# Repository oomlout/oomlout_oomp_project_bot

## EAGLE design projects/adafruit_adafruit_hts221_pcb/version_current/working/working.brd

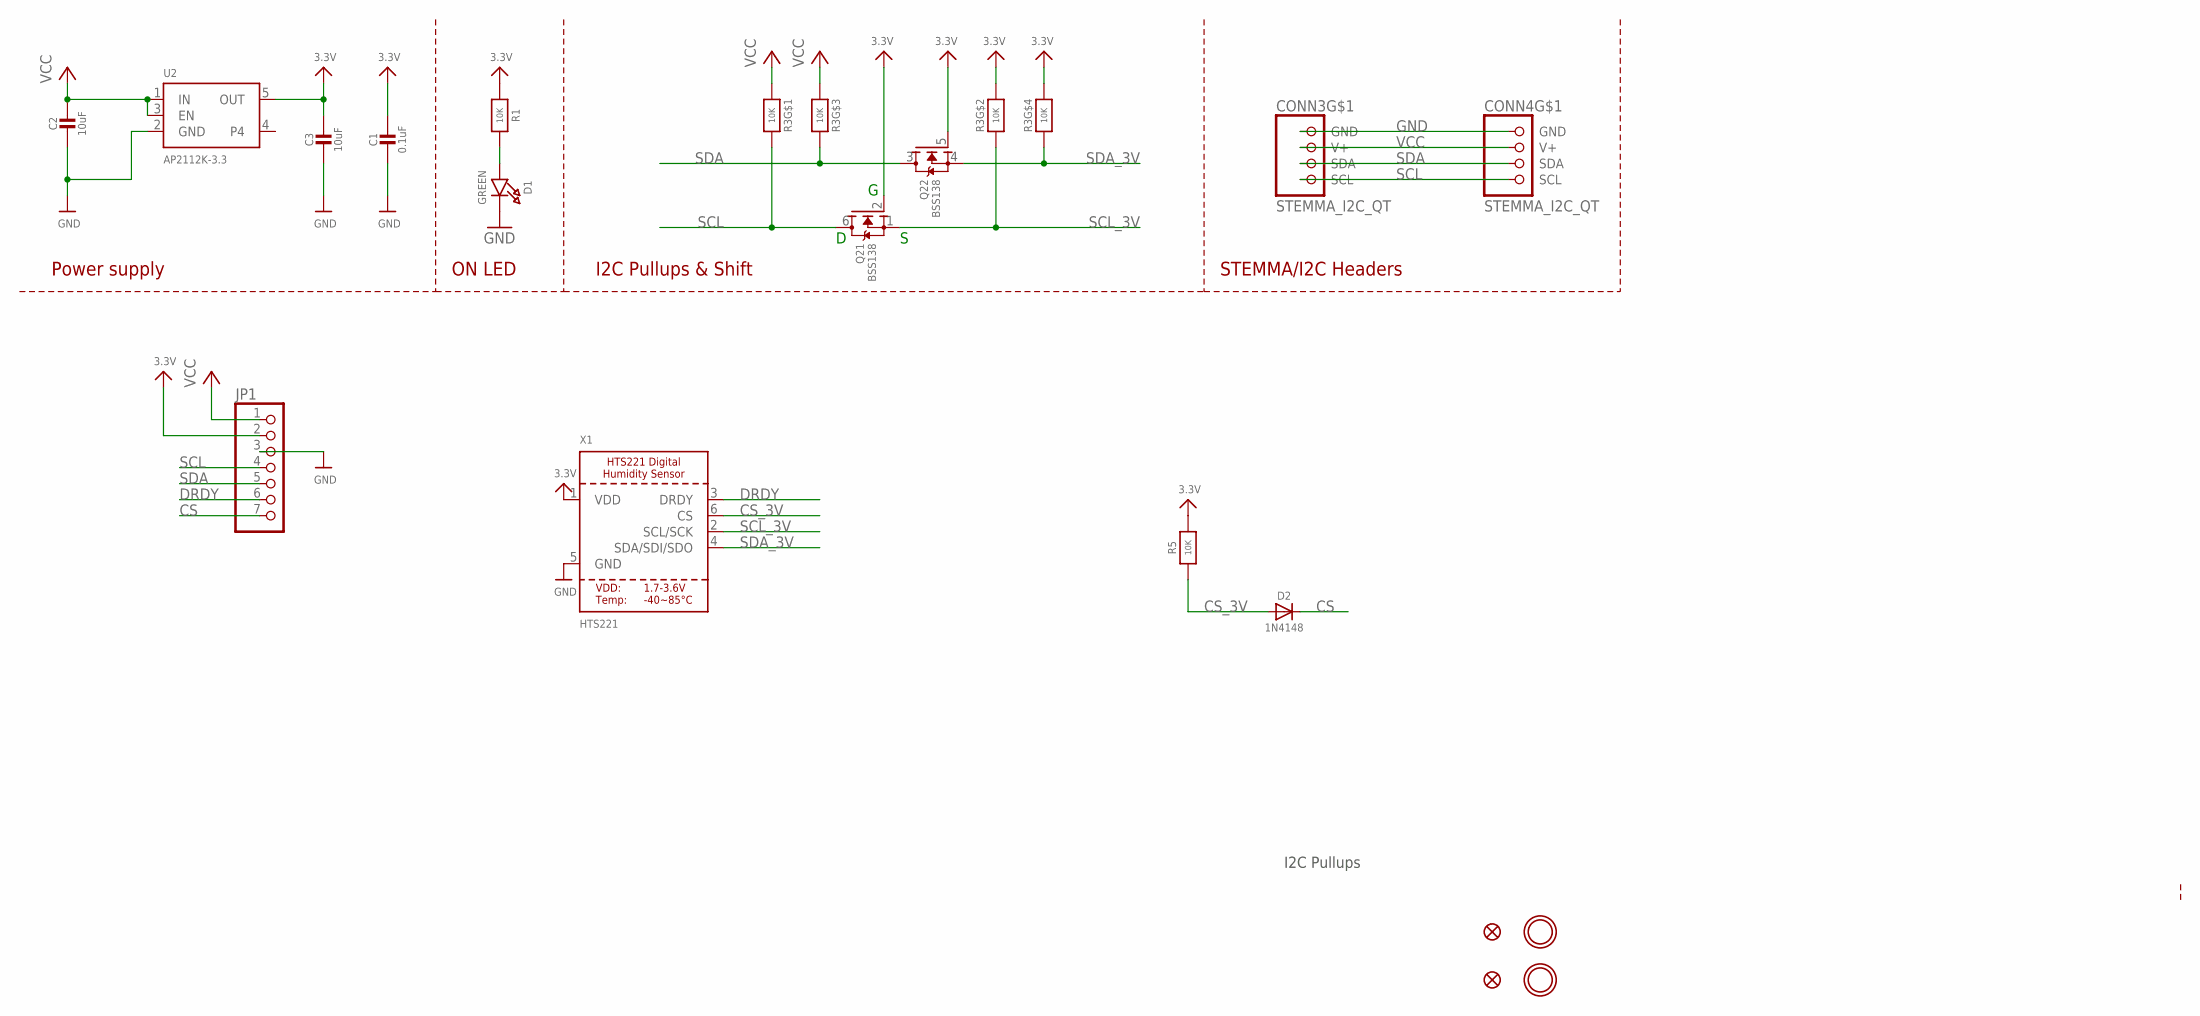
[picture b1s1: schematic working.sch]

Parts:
C1: 0.1uF; 0603-NO
C2, C3: 10uF; 0805-NO
CONN3, CONN4: STEMMA_I2C_QT; JST_SH4
D1: GREEN; CHIPLED_0603_NOOUTLINE
D2: 1N4148; SOD-323
FID3, FID4: FIDUCIAL_1MM
JP1: HEADER-1X770MIL; 1X07_ROUND_70
Q2: BSS138; SOT363
R1, R5: 10K; 0603-NO
R3: 10K; RESPACK_4X0603
U2: AP2112K-3.3; SOT23-5
U$1, U$17: MOUNTINGHOLE2.5; MOUNTINGHOLE_2.5_PLATED
X1: HTS221; HLGA-6L

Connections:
3.3V: C1.1, C3.1, JP1.2, Q2.2 (G), Q2.5 (G), R1.1, R3.2 (1), R3.4 (1), R5.2, U2.5 (OUT), X1.1 (VDD)
CS: D2.C, JP1.7
CS_3V: D2.A, R5.1, X1.6 (CS)
DRDY: JP1.6, X1.3 (DRDY)
GND: C1.2, C2.2, C3.2, CONN3.1 (GND), CONN4.1 (GND), D1.C, JP1.3, U2.2 (GND), X1.5 (GND)
unnamed: D1.A, R1.2
SCL: CONN3.4 (SCL), CONN4.4 (SCL), JP1.4, Q2.6 (D), R3.8 (2)
SCL_3V: Q2.1 (S), R3.7 (2), X1.2 (SCL/SCK)
SDA: CONN3.3 (SDA), CONN4.3 (SDA), JP1.5, Q2.3 (D), R3.6 (2)
SDA_3V: Q2.4 (S), R3.5 (2), X1.4 (SDA/SDI/SDO)
VCC: C2.1, CONN3.2 (V+), CONN4.2 (V+), JP1.1, R3.1, R3.3 (1), U2.1 (IN), U2.3 (EN)

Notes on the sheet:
I2C Pullups & Shift
STEMMA/I2C Headers
ON LED
Power supply
I2C Pullups

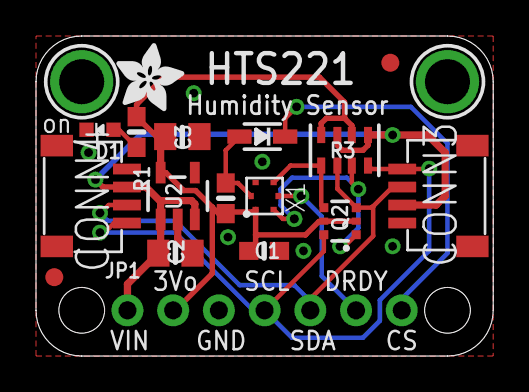
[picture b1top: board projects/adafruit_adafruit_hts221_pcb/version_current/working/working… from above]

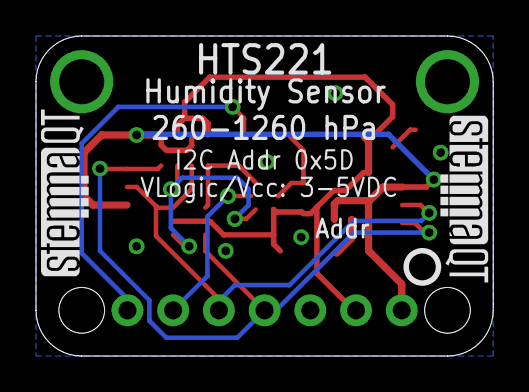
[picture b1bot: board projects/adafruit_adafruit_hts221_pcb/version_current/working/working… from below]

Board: 2 copper layers, 25.4 x 17.8 mm, 22 parts (3 on the bottom side), 11 nets.

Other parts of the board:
U$4: ADAFRUIT_3.5MM
U$25: PCBFEAT-REV-040
U$30, U$31: STEMMAQT

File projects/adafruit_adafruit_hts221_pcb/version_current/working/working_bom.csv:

Row,Description,Part,References,Value,Footprint,Quantity Per PCB,Status,Datasheet
1,,CAP_CERAMIC0603_NO,C1,0.1uF,0603-NO,1, ,
2,,CAP_CERAMIC0805-NOOUTLINE,C2 C3,10uF,0805-NO,2, ,
3,,STEMMA_I2C_QT,CONN3 CONN4,STEMMA_I2C_QT,JST_SH4,2, ,
4,,DIODESOD-323,D2,1N4148,SOD-323,1, ,
5,,LED0603_NOOUTLINE,D1,GREEN,CHIPLED_0603_NOOUTLINE,1, ,
6,,HEADER-1X770MIL,JP1,HEADER-1X770MIL,1X07_ROUND_70,1, ,
7,,MOSFET-N_DUAL,Q2,BSS138,SOT363,1, ,
8,,RESISTOR_0603_NOOUT,R1 R5,10K,0603-NO,2, ,
9,,RESISTOR_4PACK,R3,10K,RESPACK_4X0603,1, ,
10,,VREG_SOT23-5,U2,AP2112K-3.3,SOT23-5,1, ,
11,,HTS221,X1,HTS221,HLGA-6L,1, ,





Project info:
Schematic:,working
Variant:,default
Revision:,
Date:,2023-08-03_17-21-22
KiCad Version:,7.0.6-7.0.6~ubuntu22.04.1
Statistics:
Component Groups:,11
Component Count:,14 (0 SMD/ 0 THT)
Fitted Components:,14 (0 SMD/ 0 THT)
Number of PCBs:,1
Total Components:,14

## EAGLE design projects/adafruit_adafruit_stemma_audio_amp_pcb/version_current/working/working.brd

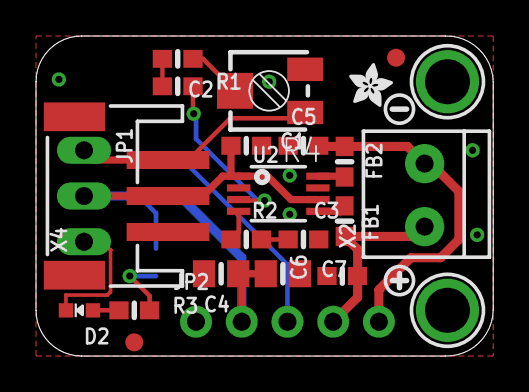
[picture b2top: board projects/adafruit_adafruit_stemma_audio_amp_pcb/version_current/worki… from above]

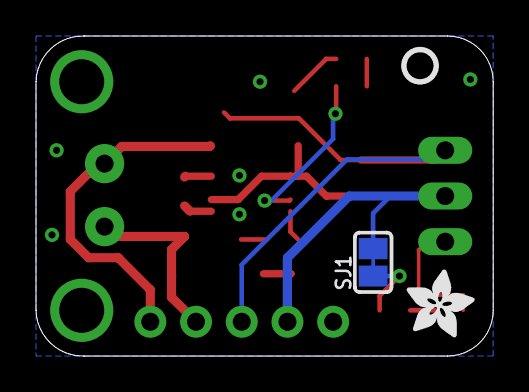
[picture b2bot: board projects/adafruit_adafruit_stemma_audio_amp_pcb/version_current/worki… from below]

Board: 2 copper layers, 25.4 x 17.8 mm, 42 parts (13 on the bottom side), 14 nets.

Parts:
C1, C2, C3: 0.1uF; 0603-NO
C4, C7: 10uF; 0805-NO
C5, C6: 220pF; 0603-NO
D2: GREEN; CHIPLED_0603_NOOUTLINE
FB1, FB2: Ferrite; 0603-NO
FID2, FID3: FIDUCIAL_1MM
JP1: 0.1" Header; 1X03_OVAL
JP2: 1X05_ROUND_70
PLABEL0: PLABEL0
PLABEL1: PLABEL1
PLABEL2: PLABEL2
PLABEL3: PLABEL3
PLABEL4: PLABEL4
PLABEL5: PLABEL5
PLABEL6: PLABEL6
PLABEL7: PLABEL7
PLABEL8: PLABEL8
PLABEL9: PLABEL9
PLABEL10: PLABEL10
PLABEL11: PLABEL11
PLABEL12: PLABEL12
R1, R2: 30K; 0603-NO
R3: 10K; 0603-NO
R4: 10K Trim; RTRIM3314J
SJ1: SOLDERJUMPER_CLOSEDWIRE
U2: PAM8302; MSOP8_0.65MM
U$1, U$8: MOUNTINGHOLE2.5; MOUNTINGHOLE_2.5_PLATED
U$3: SYMBOL_PLUS
U$5: PCBFEAT-REV-040
U$9: SYMBOL_MINUS
U$12: ADAFRUIT_3.5MM
U$19: ADAFRUIT_2.5MM
X2: 3.5mm; TERMBLOCK_1X2-3.5MM
X4: JST PH 3; JSTPH3

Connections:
GND: C1.2, C3.2, C4.2, C5.2, C6.2, C7.2, D2.C, JP1.3, JP2.1, R4.1, U2.7, X4.1
IN+: R1.2, U2.3
IN-: R2.2, U2.4
unnamed: R3.2, SJ1.1
unnamed: C3.1, R2.1
unnamed: C2.1, R1.1
unnamed: C2.2, R4.2
unnamed: D2.A, R3.1
OUT+: FB1.1, U2.5
OUT-: FB2.1, U2.8
SIGNAL: JP1.1, JP2.3, R4.3, X4.3
VIN: C1.1, C4.1, C7.1, JP1.2, JP2.2, SJ1.2, U2.1, U2.6, X4.2
VO+: C6.1, FB1.2, JP2.4, X2.2
VO-: C5.1, FB2.2, JP2.5, X2.1

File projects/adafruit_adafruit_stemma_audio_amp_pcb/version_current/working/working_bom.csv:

Row,Description,Part,References,Value,Footprint,Quantity Per PCB,Status,Datasheet
1,,CAP_CERAMIC0603_NO,C5 C6,220pF,0603-NO,2, ,
2,,CAP_CERAMIC0603_NO,C1 C2 C3,0.1uF,0603-NO,3, ,
3,,CAP_CERAMIC0805-NOOUTLINE,C4 C7,10uF,0805-NO,2, ,
4,,LED0603_NOOUTLINE,D2,GREEN,CHIPLED_0603_NOOUTLINE,1, ,
5,,FERRITE-0603NO,FB1 FB2,Ferrite,0603-NO,2, ,
6,,HEADER-1X3,JP1,"0.1"" Header",1X03_OVAL,1, ,
7,,HEADER-1X570MIL,JP2,HEADER-1X570MIL,1X05_ROUND_70,1, ,
8,,RESISTOR_0603_NOOUT,R3,10K,0603-NO,1, ,
9,,R-TRIMM3314J,R4,10K Trim,RTRIM3314J,1, ,
10,,RESISTOR_0603_NOOUT,R1 R2,30K,0603-NO,2, ,
11,,AUDIOAMP_PAM8302A,U2,PAM8302,MSOP8_0.65MM,1, ,
12,,TERMBLOCK_1X2_3.5MM,X2,3.5mm,TERMBLOCK_1X2-3.5MM,1, ,
13,,CON_JST_PH_3PIN,X4,JST PH 3,JSTPH3,1, ,





Project info:
Schematic:,working
Variant:,default
Revision:,
Date:,2023-08-03_17-21-23
KiCad Version:,7.0.6-7.0.6~ubuntu22.04.1
Statistics:
Component Groups:,13
Component Count:,19 (0 SMD/ 0 THT)
Fitted Components:,19 (0 SMD/ 0 THT)
Number of PCBs:,1
Total Components:,19

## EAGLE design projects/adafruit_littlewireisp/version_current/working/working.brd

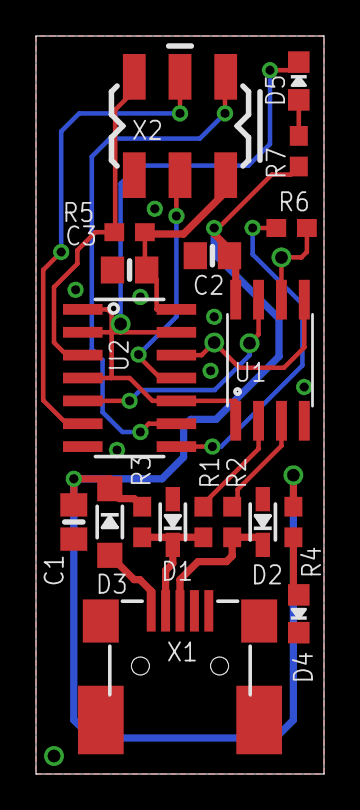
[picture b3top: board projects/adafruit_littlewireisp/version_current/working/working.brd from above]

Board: 2 copper layers, 16.0 x 41.0 mm, 19 parts (0 on the bottom side), 19 nets.

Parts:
C1: 4u7; 0805-NO
C2, C3: 100n; 0805-NO
D1, D2: 3V6; SOD-323
D3: SOD-123
D4, D5: CHIPLED_0805_NOOUTLINE
R1, R2: 68R; 0603-NO
R3: 1K5; 0603-NO
R4, R6: 470R; 0603-NO
R5: 10K; 0603-NO
R7: 1K; 0603-NO
U1: ATTINY45; SO08-EIAJ
U2: 74AHC125-SOIC14; SOIC14
X1: USB-MINIB_LARGER
X2: AVR ISP; 2X3_SMD

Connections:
5.0V: C1.1, C2.2, D3.C, R3.2, R4.1, R7.1, U1.8
GND: C1.2, C2.1, C3.1, D1.A, D2.A, D4.C, U1.4, U2.7, X1.GND, X1.GND1, X1.GND2, X1.GND3, X1.GND4, X2.6
MISO-HV: R6.1, U2.8
MISO-LV: U2.9, X2.1
MOSI-HV: U1.5, U2.12
MOSI-LV: U2.11, X2.4
unnamed: D1.C, R1.1, R3.1, X1.D-
unnamed: D2.C, R2.1, X1.D+
unnamed: D5.A, R7.2
unnamed: R1.2, U1.2
unnamed: R2.2, U1.3
unnamed: D3.A, X1.VBUS
unnamed: D4.A, R4.2
PB2/MISO: R6.2, U1.6
RST-HV: D5.C, U1.1, U2.1, U2.2, U2.4, U2.10, U2.13
RST-LV: R5.1, U2.3, X2.5
SCK-HV: U1.7, U2.5
SCK-LV: U2.6, X2.3
VDDIO: C3.2, R5.2, U2.14, X2.2

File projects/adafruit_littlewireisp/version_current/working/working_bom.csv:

Row,Description,Part,References,Value,Footprint,Quantity Per PCB,Status,Datasheet
1,,CAP_CERAMIC0805-NOOUTLINE,C2 C3,100n,0805-NO,2, ,
2,,CAP_CERAMIC0805-NOOUTLINE,C1,4u7,0805-NO,1, ,
3,,DIODE-ZENERSOD323,D1 D2,3V6,SOD-323,2, ,
4,,DIODESOD-123,D3,DIODESOD-123,SOD-123,1, ,
5,,LED0805_NOOUTLINE,D4 D5,LED0805_NOOUTLINE,CHIPLED_0805_NOOUTLINE,2, ,
6,,RESISTOR_0603_NOOUT,R1 R2,68R,0603-NO,2, ,
7,,RESISTOR_0603_NOOUT,R4 R6,470R,0603-NO,2, ,
8,,RESISTOR_0603_NOOUT,R7,1K,0603-NO,1, ,
9,,RESISTOR_0603_NOOUT,R3,1K5,0603-NO,1, ,
10,,RESISTOR_0603_NOOUT,R5,10K,0603-NO,1, ,
11,,74125-SOIC14,U2,74125-SOIC14,SOIC14,1, ,
12,,ATTINY45,U1,ATTINY45,SO08-EIAJ,1, ,
13,,AVR_SPI_PRG_6SMD,X2,AVR_SPI_PRG_6SMD,2X3_SMD,1, ,
14,,USBMINIBLARGE,X1,USBMINIBLARGE,USB-MINIB_LARGER,1, ,





Project info:
Schematic:,working
Variant:,default
Revision:,
Date:,2023-08-03_17-21-23
KiCad Version:,7.0.6-7.0.6~ubuntu22.04.1
Statistics:
Component Groups:,14
Component Count:,19 (0 SMD/ 0 THT)
Fitted Components:,19 (0 SMD/ 0 THT)
Number of PCBs:,1
Total Components:,19

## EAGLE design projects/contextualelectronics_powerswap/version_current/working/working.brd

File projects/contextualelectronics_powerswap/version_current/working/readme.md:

# PowerSwap by ContextualElectronics  
This is a harvested standardized copy of a project from github.  
The original project can be found at:  
https://github.com/ContextualElectronics/PowerSwap  
Please consult that link for additional, details, files, and license information.  
Note: It was auto harvested and if the original repo had more than one board file or anything out of the ordinary the files here are likely not representative.

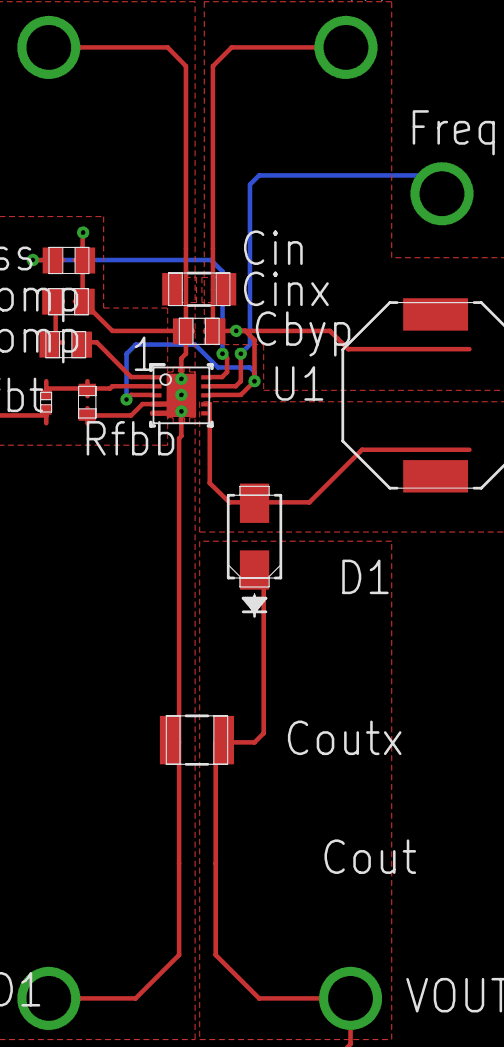
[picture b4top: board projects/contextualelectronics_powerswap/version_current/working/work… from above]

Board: 4 copper layers, 16 parts (0 on the bottom side), 9 nets.

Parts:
Cbyp: 0805
Ccomp: 0805
Cin: 1206
Cout: 1210
Css: 0805
D1: SMA
Freq: TP-1502
GND, GND1: TP-1502
L1: SRU1048
Rcomp: 0805
Rfbb: 0603
Rfbt: 0402
U1: DRC0010A
VIN: TP-1502
VOUT: TP-1502

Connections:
0: Cbyp.2, Ccomp.2, Cin.2, Cout.2, Css.2, GND.1, GND1.1, Rfbb.2, U1.4, U1.5, U1.11
1: Cbyp.1, Cin.1, L1.1, U1.3, U1.8, VIN.1
2: Cout.1, D1.1, Rfbt.1, VOUT.1
4: D1.2, L1.2, U1.6, U1.7
5: Rcomp.1, U1.1
6: Rfbb.1, Rfbt.2, U1.2
7: Ccomp.1, Rcomp.2
13: Freq.1, U1.9
14: Css.1, U1.10

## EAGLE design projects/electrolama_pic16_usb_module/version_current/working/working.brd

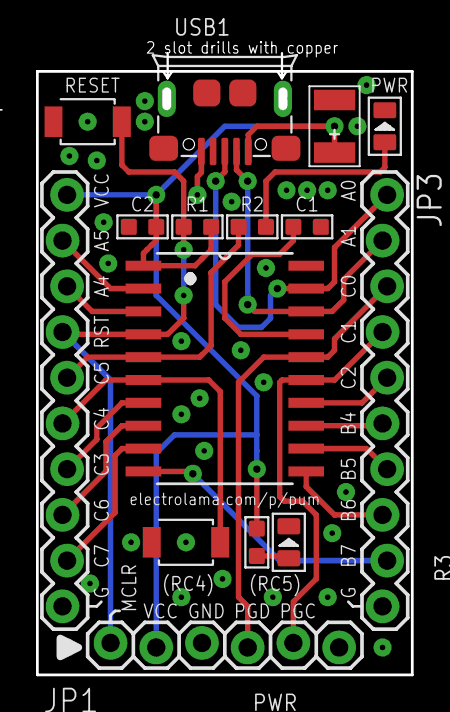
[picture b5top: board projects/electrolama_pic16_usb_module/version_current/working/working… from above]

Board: 2 copper layers, 20.8 x 34.5 mm, 15 parts (0 on the bottom side), 22 nets.

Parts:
C1: 1uf; C0603
C2: 100nf; C0603
C3: 22uf; AVX-B
D1: GREEN-0805; LED-0805
D2: YELLOW-0805; LED-0805
JP1: 1X06_LOCK
JP2, JP3: M10LOCK; 1X10_LOCK
R1: 10K; R0603
R2, R3: 200R 1/10W; R0603
SW1, SW2: B3U-1000P-2P-SMD; SW2-2.6-3.0X2.5X1.2+0.4MM
U1: PIC16F1459-I/SO; SOIC127P1030X265-20N
USB1: ST-USB-001G; MICRO-USB5+4P-SMD-0.65-B

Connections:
GND: C1.1, C2.1, C3.-, D1.-, D2.-, JP1.3, JP2.10, JP3.10, SW1.2, SW2.2, U1.20, USB1.5
MCLR: JP1.1, JP2.4, R1.1, SW1.1, U1.4
unnamed: D2.+, R2.2
unnamed: D1.+, R3.2
RA0/DP: JP3.1, U1.19, USB1.3
RA1/DM: JP3.2, U1.18, USB1.2
RA4: JP2.3, U1.3
RA5: JP2.2, U1.2
RB4: JP3.6, U1.13
RB5: JP3.7, U1.12
RB6: JP3.8, U1.11
RB7: JP3.9, U1.10
RC0/PGD: JP1.4, JP3.3, U1.16
RC1/PGC: JP1.5, JP3.4, U1.15
RC2: JP3.5, U1.14
RC3: JP2.7, U1.7
RC4: JP2.6, SW2.1, U1.6
RC5: JP2.5, R2.1, U1.5
RC6: JP2.8, U1.8
RC7: JP2.9, U1.9
VCC: C2.2, C3.+, JP1.2, JP2.1, R1.2, R3.1, U1.1, USB1.1
VUSB: C1.2, U1.17

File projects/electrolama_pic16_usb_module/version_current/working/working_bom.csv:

"Id";"Designator";"Footprint";"Quantity";"Designation";"Supplier and ref";
1;"JP1";"1X06_LOCK";1;"";;;
2;"USB1";"MICRO-USB5+4P-SMD-0.65-B";1;"ST-USB-001G";;;
3;"C2";"C0603";1;"100nf";;;
4;"SW1,SW2";"SW2-2.6-3.0X2.5X1.2+0.4MM";2;"B3U-1000P-2P-SMD";;;
5;"D2";"LED-0805";1;"YELLOW-0805";;;
6;"C3";"AVX-B";1;"22uf";;;
7;"JP3,JP2";"1X10_LOCK";2;"M10LOCK";;;
8;"U1";"SOIC127P1030X265-20N";1;"PIC16F1459-I/SO";;;
9;"R2,R3";"R0603";2;"200R 1/10W";;;
10;"D1";"LED-0805";1;"GREEN-0805";;;
11;"C1";"C0603";1;"1uf";;;
12;"R1";"R0603";1;"10K";;;

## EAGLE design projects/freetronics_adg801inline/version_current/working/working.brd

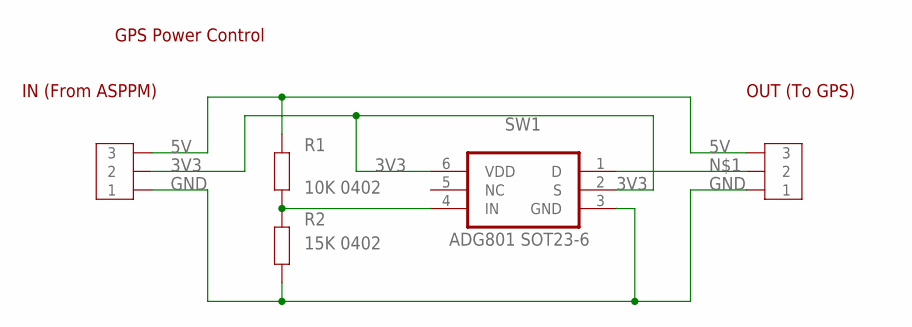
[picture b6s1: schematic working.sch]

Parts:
JP1, JP2: 3PIN_SMD; 1X3-2MM
R1: 10K 0402; 0402
R2: 15K 0402; 0402
SW1: ADG801 SOT23-6; SOT23-6

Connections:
3V3: JP1.P$2 (2), SW1.2 (S), SW1.6 (VDD)
5V: JP1.P$3 (3), JP2.P$3 (3), R1.2
GND: JP1.P$1 (1), JP2.P$1 (1), R2.1, SW1.3 (GND)
unnamed: JP2.P$2 (2), SW1.1 (D)
unnamed: R1.1, R2.2, SW1.4 (IN)

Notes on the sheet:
GPS Power Control
IN (From ASPPM)
OUT (To GPS)

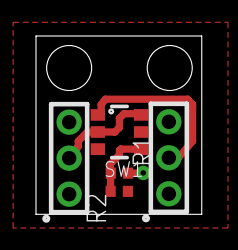
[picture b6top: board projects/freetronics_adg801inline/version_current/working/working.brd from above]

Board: 4 copper layers, 9.2 x 9.9 mm, 5 parts (0 on the bottom side), 5 nets.

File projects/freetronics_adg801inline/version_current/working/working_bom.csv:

"Id";"Designator";"Footprint";"Quantity";"Designation";"Supplier and ref";
1;"@HOLE0,@HOLE1";"";2;"";;;
2;"R1";"0402";1;"10K 0402";;;
3;"JP1,JP2";"1X3-2MM";2;"";;;
4;"SW1";"SOT23-6";1;"ADG801 SOT23-6";;;
5;"R2";"0402";1;"15K 0402";;;

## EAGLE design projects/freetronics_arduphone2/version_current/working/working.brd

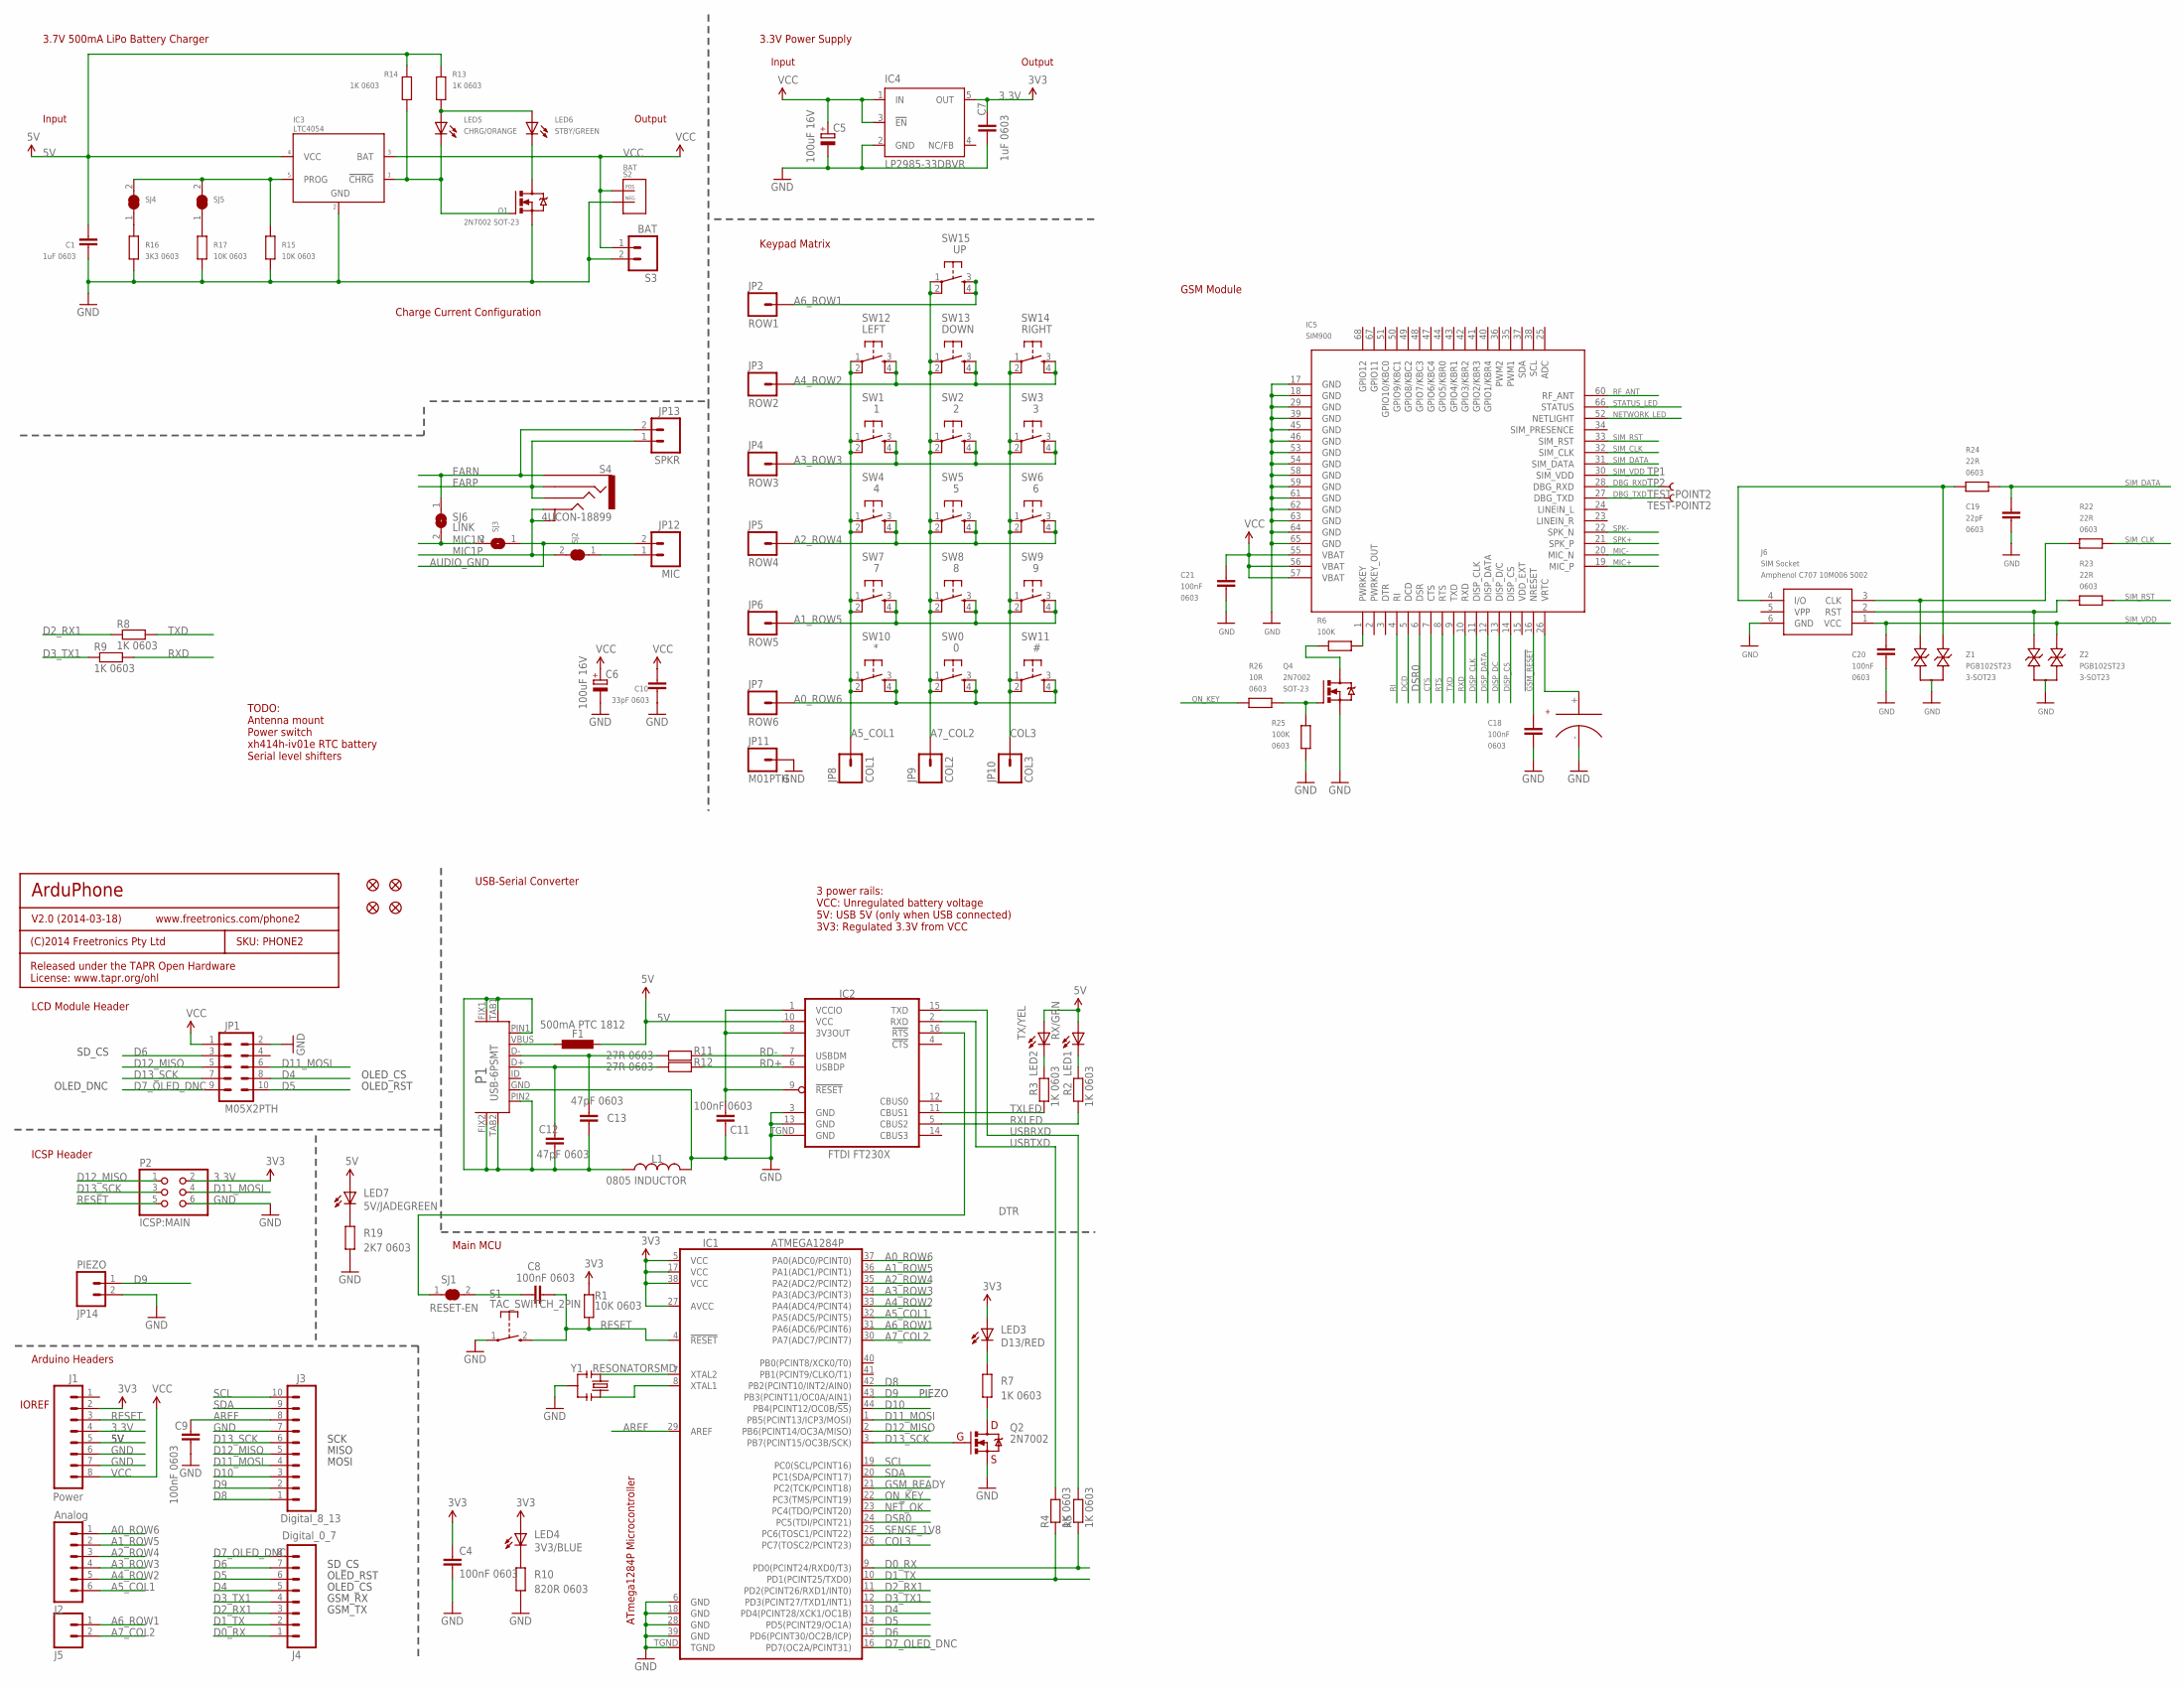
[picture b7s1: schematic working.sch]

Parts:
C1, C7: 1uF 0603; 0603
C4, C8, C9, C11: 100nF 0603; 0603
C5, C6: 100uF 16V; PANASONIC_D
C10: 33pF 0603; 0603@1
C12, C13: 47pF 0603; C0603
C18, C20, C21: 100nF; 0603
C19: 22pF; 0603
F1: 500mA PTC 1812; L1812
IC1: ATMEGA1284P; QFN-44M1
IC2: FT230X; QFN-16
IC3: LTC4054; SOT23-5
IC4: LP2985-33DBVR; TEXAS_SOT23-DBV
IC5: SIM900
J1: Power; 1X08
J2: Analog; 1X06
J3: Digital_8_13; 1X10
J4: Digital_0_7; 1X08
J5: M02PTH; 1X02
J6: SIM Socket; SIMHOLDER3
JP1: M05X2PTH; AVR_ICSP
JP2: ROW1; 1X01
JP3: ROW2; 1X01
JP4: ROW3; 1X01
JP5: ROW4; 1X01
JP6: ROW5; 1X01
JP7: ROW6; 1X01
JP8: COL1; 1X01
JP9: COL2; 1X01
JP10: COL3; 1X01
JP11: M01PTH; 1X01
JP12: MIC; 1X02
JP13: SPKR; 1X02
JP14: PIEZO; 1X02
L1: 0805 INDUCTOR; 0805-LARGE
LED1: RX/GRN; LED-0603
LED2: TX/YEL; LED-0603
LED3: D13/RED; LED-0603
LED4: 3V3/BLUE; LED-0603
LED5: CHRG/ORANGE; LED-0603
LED6: STBY/GREEN; LED-0603
LED7: 5V/JADEGREEN; LED-0603
P1: USB-6PSMT; USB-MICROB-MB05PMXX
P2: ICSP:MAIN; 2X03
Q1: 2N7002 SOT-23; SOT23-3
Q2, Q4: 2N7002; SOT23-3
R1, R15, R17: 10K 0603; 0603
R2, R3, R4, R5, R7, R8, R9, R13, R14: 1K 0603; 0603
R6, R25: 100K; 0603
R10: 820R 0603; 0603
R11, R12: 27R 0603; 0603
R16: 3K3 0603; 0603
R19: 2K7 0603; 0603
R22, R23, R24: 22R; 0603
R26: 10R; 0603
S1: TAC_SWITCH_2PIN; TACTILE_SWITCH_SMD_2PIN_TINY
S2: BAT; JST-2MM-TH-RA
S3: BAT; 1X02
S4: 4UCON-18899
SJ1: RESET-EN; SJC
SJ2, SJ4, SJ5: SJCN; SJC
SJ3: SJ
SJ6: LINK; SJ
SW0: 0; TACTILE-PTH
SW1: 1; TACTILE-PTH
SW2: 2; TACTILE-PTH
SW3: 3; TACTILE-PTH
SW4: 4; TACTILE-PTH
SW5: 5; TACTILE-PTH
SW6: 6; TACTILE-PTH
SW7: 7; TACTILE-PTH
SW8: 8; TACTILE-PTH
SW9: 9; TACTILE-PTH
SW10: *; TACTILE-PTH
SW11: #; TACTILE-PTH
SW12: LEFT; TACTILE-PTH
SW13: DOWN; TACTILE-PTH
SW14: RIGHT; TACTILE-PTH
SW15: UP; TACTILE-PTH
TP1, TP2: TEST-POINT2; PAD.02X.02
U$5, U$6, U$7, U$14: FIDUCIAL1X2.5; FIDUCIAL-1X2.5
U$9: XH414H-IV01E; 414-VA5R
Y1: RESONATORSMD; RESONATOR-SMD
Z1, Z2: PGB102ST23; SOT23-3

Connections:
3.3V: C4.1, C7.2, IC1.5 (VCC), IC1.17 (VCC), IC1.27 (AVCC), IC1.38 (VCC), IC4.5 (OUT), J1.2, J1.4, LED3.A, LED4.A, P2.2, R1.2
5V: C1.2, F1.2, IC2.10 (VCC), IC3.4 (VCC), J1.5, LED1.A, LED2.A, LED7.A, R13.1, R14.1
!GSM_RESET: C18.2, IC5.16 (NRESET)
A0_ROW6: IC1.37 (PA0(ADC0/PCINT0)), J2.1, JP7.1, SW0.3, SW0.4, SW10.3, SW10.4, SW11.3, SW11.4
A1_ROW5: IC1.36 (PA1(ADC1/PCINT1)), J2.2, JP6.1, SW7.3, SW7.4, SW8.3, SW8.4, SW9.3, SW9.4
A2_ROW4: IC1.35 (PA2(ADC2/PCINT2)), J2.3, JP5.1, SW4.3, SW4.4, SW5.3, SW5.4, SW6.3, SW6.4
A3_ROW3: IC1.34 (PA3(ADC3/PCINT3)), J2.4, JP4.1, SW1.3, SW1.4, SW2.3, SW2.4, SW3.3, SW3.4
A4_ROW2: IC1.33 (PA4(ADC4/PCINT4)), J2.5, JP3.1, SW12.3, SW12.4, SW13.3, SW13.4, SW14.3, SW14.4
A5_COL1: IC1.32 (PA5(ADC5/PCINT5)), J2.6, JP8.1, SW1.1, SW1.2, SW4.1, SW4.2, SW7.1, SW7.2, SW10.1, SW10.2, SW12.1, SW12.2
A6_ROW1: IC1.31 (PA6(ADC6/PCINT6)), J5.1, JP2.1, SW15.3, SW15.4
A7_COL2: IC1.30 (PA7(ADC7/PCINT7)), J5.2, JP9.1, SW0.1, SW0.2, SW2.1, SW2.2, SW5.1, SW5.2, SW8.1, SW8.2, SW13.1, SW13.2, SW15.1, SW15.2
AREF: C9.1, IC1.29 (AREF), J3.8
AUDIO_GND: JP12.2, SJ3.1
COL3: IC1.26 (PC7(TOSC2/PCINT23)), JP10.1, SW3.1, SW3.2, SW6.1, SW6.2, SW9.1, SW9.2, SW11.1, SW11.2, SW14.1, SW14.2
CTS: IC5.7 (CTS)
D0_RX: IC1.9 (PD0(PCINT24/RXD0/T3)), J4.1, R5.1
D1_TX: IC1.10 (PD1(PCINT25/TXD0)), J4.2, R4.1
D2_RX1: IC1.11 (PD2(PCINT26/RXD1/INT0)), J4.3, R8.1
D3_TX1: IC1.12 (PD3(PCINT27/TXD1/INT1)), J4.4, R9.1
D4: IC1.13 (PD4(PCINT28/XCK1/OC1B)), J4.5, JP1.8
D5: IC1.14 (PD5(PCINT29/OC1A)), J4.6, JP1.10
D6: IC1.15 (PD6(PCINT30/OC2B/ICP)), J4.7, JP1.3
D7_OLED_DNC: IC1.16 (PD7(OC2A/PCINT31)), J4.8, JP1.9
D8: IC1.42 (PB2(PCINT10/INT2/AIN0)), J3.1
D9: IC1.43 (PB3(PCINT11/OC0A/AIN1)), J3.2, JP14.1
D10: IC1.44 (PB4(PCINT12/OC0B/!SS!)), J3.3
D11_MOSI: IC1.1 (PB5(PCINT13/ICP3/MOSI)), J3.4, JP1.6, P2.4
D12_MISO: IC1.2 (PB6(PCINT14/OC3A/MISO)), J3.5, JP1.5, P2.1
D13_SCK: IC1.3 (PB7(PCINT15/OC3B/SCK)), J3.6, JP1.7, P2.3, Q2.1 (G)
DBG_RXD: IC5.28 (DBG_RXD), TP1.P$1
DBG_TXD: IC5.27 (DBG_TXD), TP2.P$1
DCD: IC5.5 (DCD)
DISP_CLK: IC5.11 (DISP_CLK)
DISP_CS: IC5.14 (DISP_CS)
DISP_DATA: IC5.12 (DISP_DATA)
DISP_DC: IC5.13 (DISP_D/C)
DSR0: IC1.24 (PC5(TDI/PCINT21)), IC5.6 (DSR)
DTR: IC2.16 (!RTS), SJ1.1
EARN: JP13.2, S4.1, SJ6.1
EARP: JP13.1, S4.3, S4.4
GND: C1.1, C4.2, C5.-, C6.-, C7.1, C9.2, C10.1, C11.2, C18.1, C19.1, C20.1, C21.1, IC1.6 (GND), IC1.18 (GND), IC1.28 (GND), IC1.39 (GND), IC1.TGND, IC2.3 (GND), IC2.13 (GND), IC2.TGND (GND), IC3.2 (GND), IC4.2 (GND), IC5.17 (GND), IC5.18 (GND), IC5.29 (GND), IC5.39 (GND), IC5.45 (GND), IC5.46 (GND), IC5.53 (GND), IC5.54 (GND), IC5.58 (GND), IC5.59 (GND), IC5.61 (GND), IC5.62 (GND), IC5.63 (GND), IC5.64 (GND), IC5.65 (GND), J1.6, J1.7, J3.7, J6.6 (GND), JP1.2, JP11.1, JP14.2, L1.2, P1.GND, P2.6, Q1.2 (S), Q2.2 (S), Q4.2 (S), R10.1, R15.2, R16.2, R17.2, R19.1, R25.1, S1.1, S2.NEG, S3.2, U$9.-, Y1.2, Z1.3, Z2.3
GSM_READY: IC1.21 (PC2(TCK/PCINT18))
MIC1N: SJ3.2, SJ6.2
MIC1P: S4.2A, S4.2B, SJ2.2
MIC+: IC5.19 (MIC_P)
MIC-: IC5.20 (MIC_N)
unnamed: C8.1, SJ1.2
unnamed: C11.1, IC2.1 (VCCIO), IC2.8 (3V3OUT), IC2.9 (!RESET)
unnamed: C12.2, C13.2, L1.1, P1.FIX1, P1.FIX2, P1.PIN1, P1.PIN2, P1.TAB1, P1.TAB2
unnamed: LED3.C, R7.2
unnamed: LED6.C, Q1.3 (D)
unnamed: Q2.3 (D), R7.1
unnamed: LED7.C, R19.2
unnamed: LED5.A, LED6.A, R13.2
unnamed: IC1.7 (XTAL2), Y1.1
unnamed: IC3.1 (!CHRG), LED5.C, Q1.1 (G), R14.2
unnamed: LED1.C, R2.2
unnamed: IC3.5 (PROG), R15.1, SJ4.2, SJ5.2
unnamed: LED2.C, R3.2
unnamed: LED4.C, R10.2
unnamed: IC1.8 (XTAL1), Y1.3
unnamed: C12.1, P1.D+, R12.2
unnamed: C13.1, P1.D-, R11.2
unnamed: IC5.1 (PWRKEY), R6.2
unnamed: Q4.3 (D), R6.1
unnamed: JP12.1, SJ2.1
unnamed: J6.2 (RST), R23.2, Z2.1
unnamed: IC5.26 (VRTC), U$9.+
unnamed: R16.1, SJ4.1
unnamed: R17.1, SJ5.1
unnamed: J6.3 (CLK), R22.2, Z1.1
unnamed: J6.4 (I/O), R24.2, Z1.2
unnamed: Q4.1 (G), R25.2, R26.1
unnamed: F1.1, P1.VBUS
NETWORK_LED: IC5.52 (NETLIGHT)
NET_OK: IC1.23 (PC4(TDO/PCINT20))
ON_KEY: IC1.22 (PC3(TMS/PCINT19)), R26.2
RD+: IC2.6 (USBDP), R12.1
RD-: IC2.7 (USBDM), R11.1
RESET: C8.2, IC1.4 (!RESET), J1.3, P2.5, R1.1, S1.2 (S)
RF_ANT: IC5.60 (RF_ANT)
RI: IC5.4 (RI)
RTS: IC5.8 (RTS)
RXD: IC5.10 (RXD), R9.2
RXLED: IC2.5 (CBUS2), R2.1
SCL: IC1.19 (PC0(SCL/PCINT16)), J3.10
SDA: IC1.20 (PC1(SDA/PCINT17)), J3.9
SENSE_1V8: IC1.25 (PC6(TOSC1/PCINT22))
SIM_CLK: IC5.32 (SIM_CLK), R22.1
SIM_DATA: C19.2, IC5.31 (SIM_DATA), R24.1
SIM_RST: IC5.33 (SIM_RST), R23.1
SIM_VDD: C20.2, IC5.30 (SIM_VDD), J6.1 (VCC), Z2.2
SPK+: IC5.21 (SPK_P)
SPK-: IC5.22 (SPK_N)
STATUS_LED: IC5.66 (STATUS)
TXD: IC5.9 (TXD), R8.2
TXLED: IC2.11 (CBUS1), R3.1
USBRXD: IC2.15 (TXD), R5.2
USBTXD: IC2.2 (RXD), R4.2
VCC: C5.+, C6.+, C10.2, C21.2, IC3.3 (BAT), IC4.1 (IN), IC4.3 (!EN), IC5.55 (VBAT), IC5.56 (VBAT), IC5.57 (VBAT), J1.8, JP1.1, S2.POS, S3.1

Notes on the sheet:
ArduPhone
V2.0 (2014-03-18)
SKU: PHONE2
(C)2014 Freetronics Pty Ltd
Released under the TAPR Open Hardware License: www.tapr.org/ohl
www.freetronics.com/phone2
IOREF
ATmega1284P Microcontroller
3 power rails: VCC: Unregulated battery voltage 5V: USB 5V (only when USB connected) 3V3: Regulated 3.3V from VCC
OLED_DNC
SD_CS
OLED_CS
OLED_RST
TODO: Antenna mount Power switch xh414h-iv01e RTC battery Serial level shifters
Output
Input
3.7V 500mA LiPo Battery Charger
3.3V Power Supply
Keypad Matrix
GSM Module
LCD Module Header
USB-Serial Converter
Main MCU
Arduino Headers
ICSP Header
SCK
MISO
MOSI
GSM_RX
GSM_TX
Charge Current Configuration
PIEZO

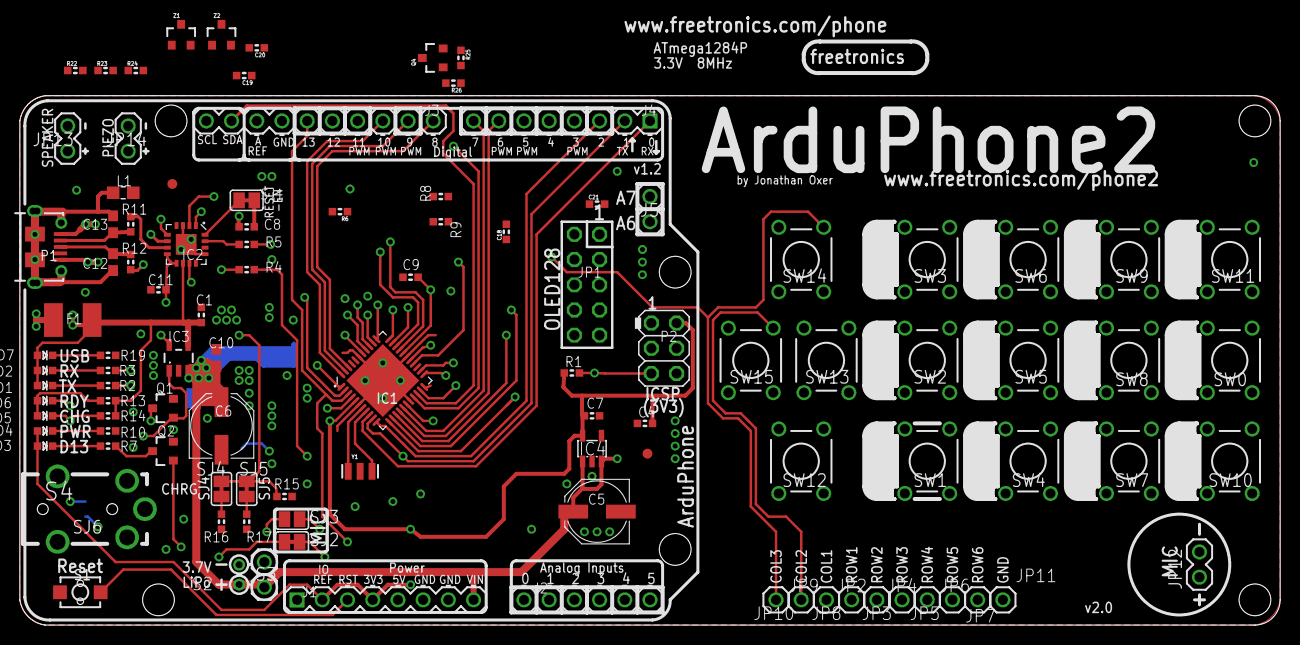
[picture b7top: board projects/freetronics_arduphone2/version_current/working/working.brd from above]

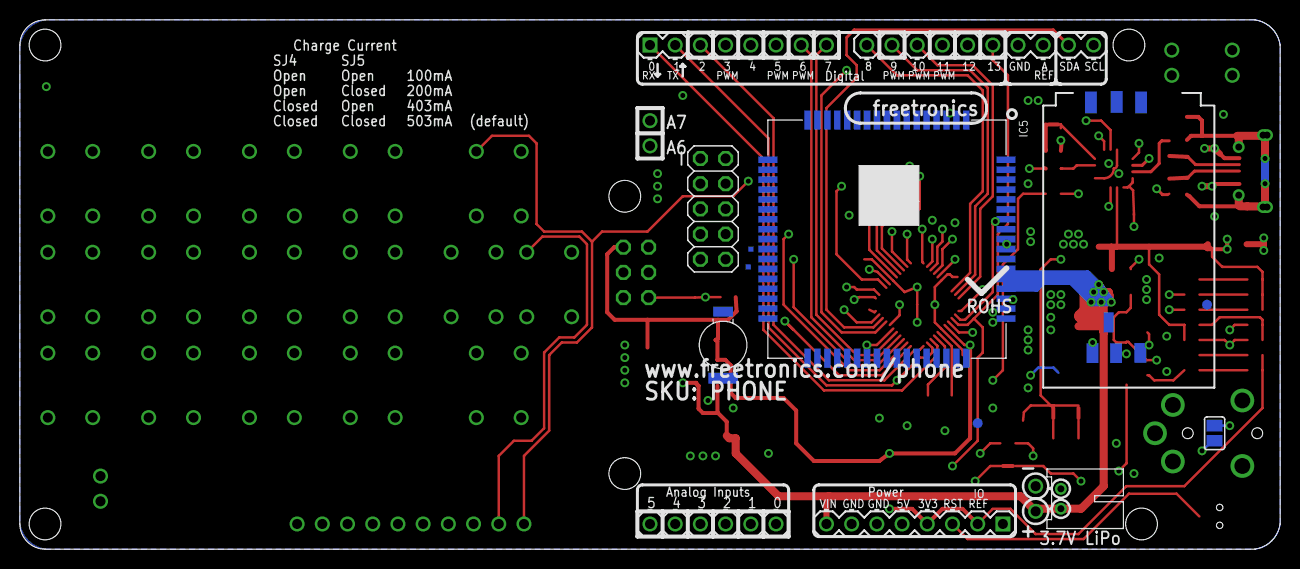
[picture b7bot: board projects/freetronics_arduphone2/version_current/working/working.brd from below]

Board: 4 copper layers, 127.0 x 53.3 mm, 113 parts (10 on the bottom side), 82 nets.

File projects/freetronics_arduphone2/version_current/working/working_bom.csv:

"Id";"Designator";"Footprint";"Quantity";"Designation";"Supplier and ref";
1;"C7,C1";"0603";2;"1uF 0603";;;
2;"J2";"1X06";1;"Analog";;;
3;"R26";"0603";1;"10R";;;
4;"R9,R4,R3,R8,R14,R5,R7,R2,R13";"0603";9;"1K 0603";;;
5;"C18,C20,C21";"0603";3;"100nF";;;
6;"LED1";"LED-0603";1;"RX/GRN";;;
7;"R25,R6";"0603";2;"100K";;;
8;"J1";"1X08";1;"Power";;;
9;"SW10";"TACTILE-PTH";1;"*";;;
10;"JP2";"1X01";1;"ROW1";;;
11;"SW9";"TACTILE-PTH";1;"9";;;
12;"@HOLE2,@HOLE1,@HOLE5,@HOLE4,@HOLE3,@HOLE0";"";6;"";;;
13;"S3";"1X02";1;"BAT";;;
14;"SW2";"TACTILE-PTH";1;"2";;;
15;"LED5";"LED-0603";1;"CHRG/ORANGE";;;
16;"LED3";"LED-0603";1;"D13/RED";;;
17;"IC2";"QFN-16";1;"FT230X";;;
18;"C10";"0603@1";1;"33pF 0603";;;
19;"JP13";"1X02";1;"SPKR";;;
20;"LED7";"LED-0603";1;"5V/JADEGREEN";;;
21;"R10";"0603";1;"820R 0603";;;
22;"SW11";"TACTILE-PTH";1;"#";;;
23;"C9,C4,C11,C8";"0603";4;"100nF 0603";;;
24;"JP14";"1X02";1;"PIEZO";;;
25;"SW4";"TACTILE-PTH";1;"4";;;
26;"SJ1";"SJC";1;"RESET-EN";;;
27;"C13,C12";"C0603";2;"47pF 0603";;;
28;"S1";"TACTILE_SWITCH_SMD_2PIN_TINY";1;"TAC_SWITCH_2PIN";;;
29;"SW0";"TACTILE-PTH";1;"0";;;
30;"S4";"4UCON-18899";1;"4UCON-18899";;;
31;"U$14,U$5,U$6,U$7";"FIDUCIAL-1X2.5";4;"FIDUCIAL1X2.5";;;
32;"IC4";"TEXAS_SOT23-DBV";1;"LP2985-33DBVR";;;
33;"JP9";"1X01";1;"COL2";;;
34;"SJ5,SJ4,SJ2";"SJC";3;"SJCN";;;
35;"JP4";"1X01";1;"ROW3";;;
36;"R17,R1,R15";"0603";3;"10K 0603";;;
37;"C6,C5";"PANASONIC_D";2;"100uF 16V";;;
38;"SW12";"TACTILE-PTH";1;"LEFT";;;
39;"R23,R24,R22";"0603";3;"22R";;;
40;"JP3";"1X01";1;"ROW2";;;
41;"SW13";"TACTILE-PTH";1;"DOWN";;;
42;"SW1";"TACTILE-PTH";1;"1";;;
43;"L1";"0805-LARGE";1;"0805 INDUCTOR";;;
44;"SJ3";"SJ";1;"";;;
45;"LED2";"LED-0603";1;"TX/YEL";;;
46;"R16";"0603";1;"3K3 0603";;;
47;"SW14";"TACTILE-PTH";1;"RIGHT";;;
48;"JP8";"1X01";1;"COL1";;;
49;"F1";"L1812";1;"500mA PTC 1812";;;
50;"SW7";"TACTILE-PTH";1;"7";;;
51;"J4";"1X08";1;"Digital_0_7";;;
52;"SW8";"TACTILE-PTH";1;"8";;;
53;"P2";"2X03";1;"ICSP:MAIN";;;
54;"JP6";"1X01";1;"ROW5";;;
55;"JP12";"1X02";1;"MIC";;;
56;"Q2,Q4";"SOT23-3";2;"2N7002";;;
57;"JP5";"1X01";1;"ROW4";;;
58;"Q1";"SOT23-3";1;"2N7002 SOT-23";;;
59;"R12,R11";"0603";2;"27R 0603";;;
60;"Z1,Z2";"SOT23-3";2;"PGB102ST23";;;
61;"SW6";"TACTILE-PTH";1;"6";;;
62;"JP10";"1X01";1;"COL3";;;
63;"J3";"1X10";1;"Digital_8_13";;;
64;"LED6";"LED-0603";1;"STBY/GREEN";;;
65;"R19";"0603";1;"2K7 0603";;;
66;"LED4";"LED-0603";1;"3V3/BLUE";;;
67;"P1";"USB-MICROB-MB05PMXX";1;"USB-6PSMT";;;
68;"IC1";"QFN-44M1";1;"ATMEGA1284P";;;
69;"SW5";"TACTILE-PTH";1;"5";;;
70;"C19";"0603";1;"22pF";;;
71;"SW15";"TACTILE-PTH";1;"UP";;;
72;"JP7";"1X01";1;"ROW6";;;
73;"SW3";"TACTILE-PTH";1;"3";;;
74;"J5";"1X02";1;"";;;
75;"IC3";"SOT23-5";1;"LTC4054";;;
76;"Y1";"RESONATOR-SMD";1;"RESONATORSMD";;;
77;"JP11";"1X01";1;"M01PTH";;;
78;"TP1,TP2";"PAD.02X.02";2;"TEST-POINT2";;;
79;"S2";"JST-2MM-TH-RA";1;"BAT";;;
80;"J6";"SIMHOLDER3";1;"SIM Socket";;;
81;"SJ6";"SJ";1;"LINK";;;
82;"U$9";"414-VA5R";1;"XH414H-IV01E";;;
83;"IC5";"SIM900";1;"SIM900";;;
84;"JP1";"AVR_ICSP";1;"M05X2PTH";;;

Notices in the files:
parts and their libraries:
microbuilder: This work is placed in the public domain, and may be freely used for commercial and non-commercial work with the following conditions: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
SparkFun-Connectors: Licensing: Creative Commons ShareAlike 4.0 International - https://creativecommons.org/licenses/by-sa/4.0
